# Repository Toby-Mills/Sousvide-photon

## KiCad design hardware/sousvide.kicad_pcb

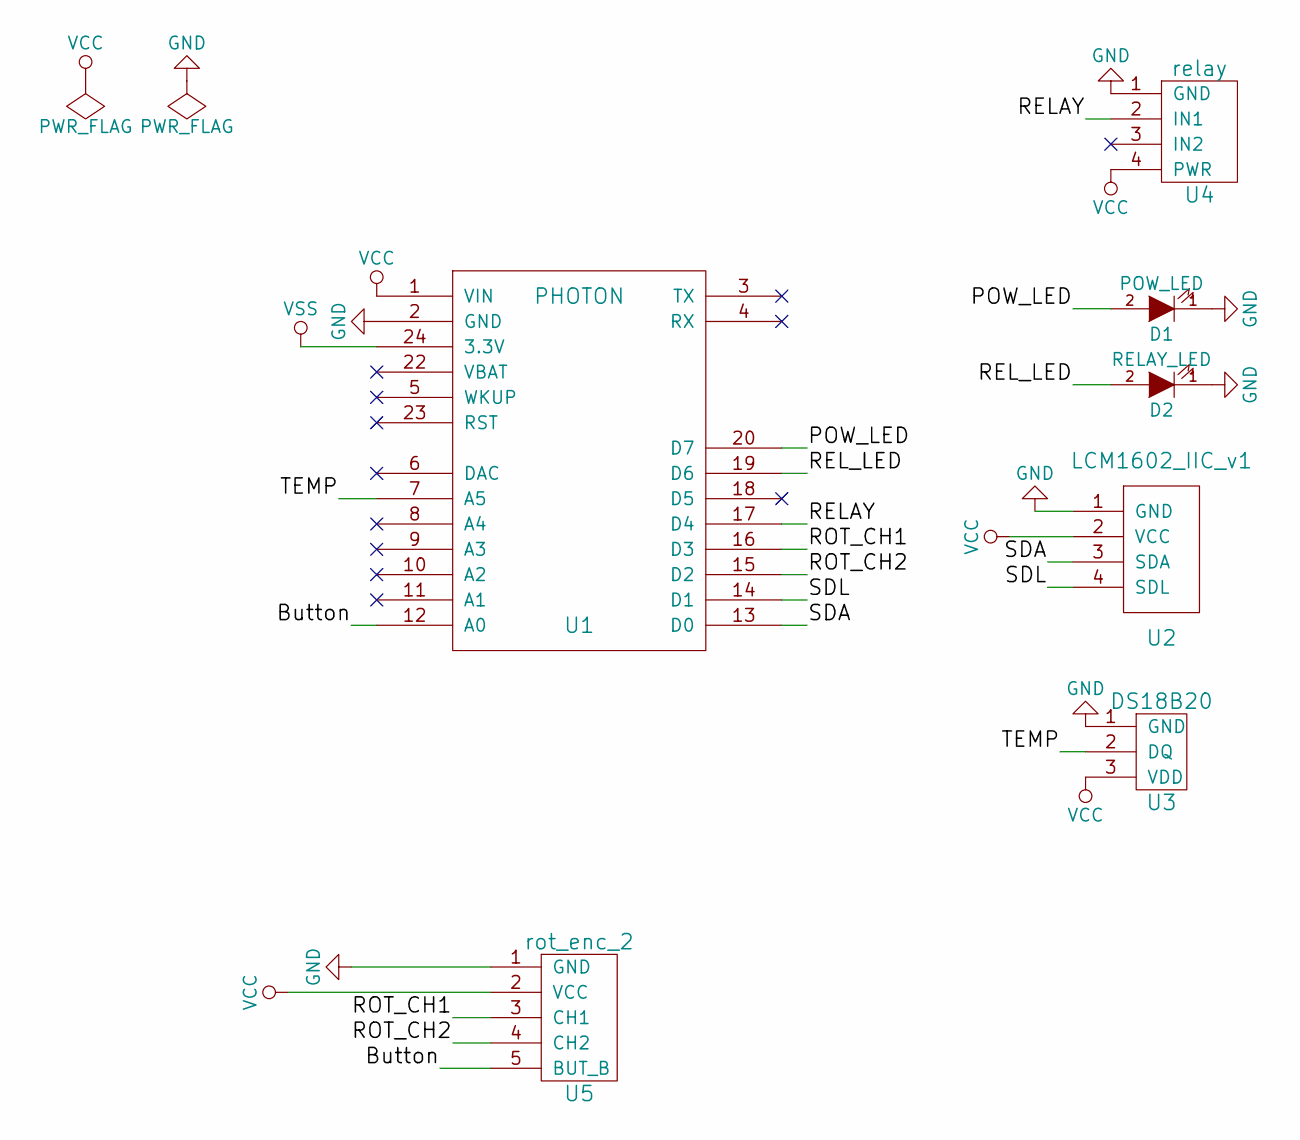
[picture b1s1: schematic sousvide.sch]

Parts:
D1: POW_LED; LED-5MM
D2: RELAY_LED; LED-5MM
U1: PHOTON; photon
U2: LCM1602_IIC_v1; Pin_Header_Straight_1x04
U3: DS18B20; Pin_Header_Straight_1x03
U4: relay; Pin_Header_Straight_1x04
U5: rot_enc_2; Pin_Header_Straight_1x05

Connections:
/Button: U1.12 (A0), U5.5 (BUT_B)
/POW_LED: D1.2 (A), U1.20 (D7)
/RELAY: U1.17 (D4), U4.2 (IN1)
/REL_LED: D2.2 (A), U1.19 (D6)
/ROT_CH1: U1.16 (D3), U5.3 (CH1)
/ROT_CH2: U1.15 (D2), U5.4 (CH2)
/SDA: U1.13 (D0), U2.3 (SDA)
/SDL: U1.14 (D1), U2.4 (SDL)
/TEMP: U1.7 (A5), U3.2 (DQ)
GND: D1.1 (K), D2.1 (K), U1.2 (GND), U2.1 (GND), U3.1 (GND), U4.1 (GND), U5.1 (GND)
VCC: U1.1 (VIN), U2.2 (VCC), U3.3 (VDD), U4.4 (PWR), U5.2 (VCC)
VSS: U1.24 (3.3V)

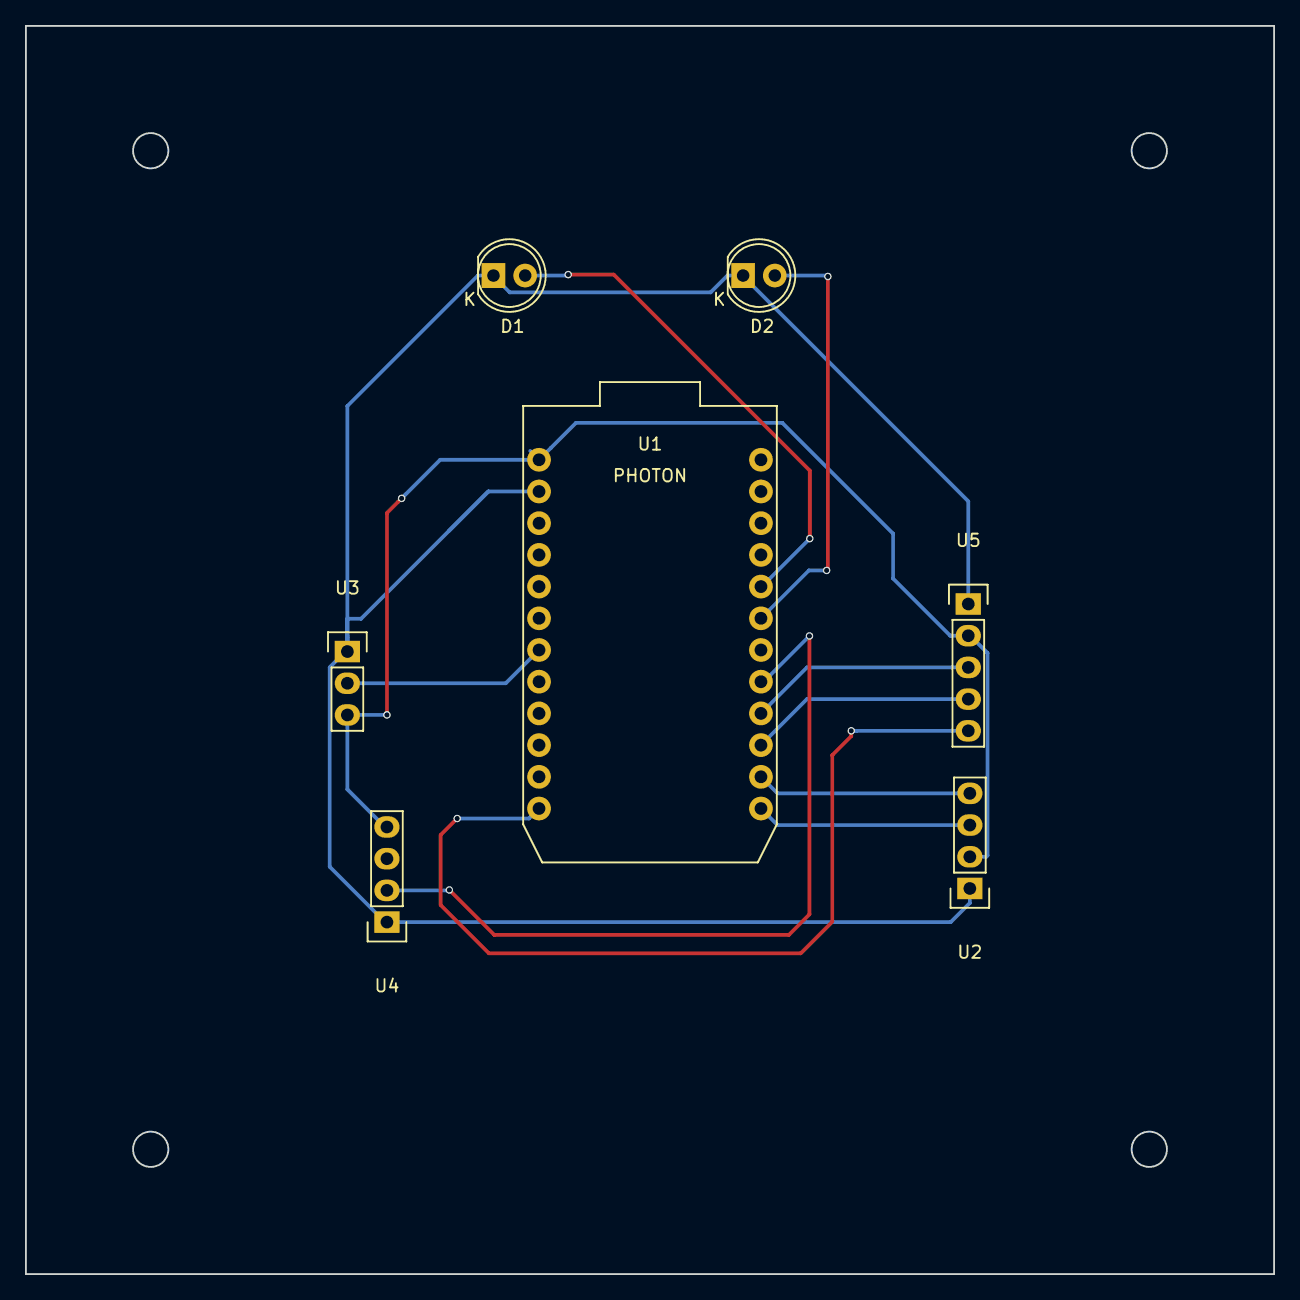
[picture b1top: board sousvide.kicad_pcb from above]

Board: 2 copper layers, 100.0 x 100.0 mm, 7 parts (0 on the bottom side), 11 nets.

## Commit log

2018-05-20 Commenting and formatting
2018-05-20 Removed unneeded makeChange code
2018-05-20 cleaned redraw screen code
    removed unneeded redrawscreeni variable
    renamed screenRedrawRelayRequest to lastScreenRedraw
2018-05-20 removed unneeded temp, ctemp and ctempm variables
2018-05-20 Removed old commented code
2018-05-20 removed unused atTemp, offset, uptime, atime variables
2018-05-20 refactored Setup() to call methods
2018-05-20 refactored code for setting desired temperature & updating display
2018-05-20 improved variable names
2018-05-20 removed unused getSavedTemp method
2018-05-20 removed unused setTitle method
2018-05-20 commenting and refactoring
2018-05-20 Removed unused variables
2018-05-20 bug fix
2018-07-18 Rotary Encoder adjusts target temp
2018-07-23 Power and Relay LED's added
2018-08-09 Exposed variables to Particle Cloud
2018-08-17 Added kicad files for controller board
2018-08-17 moved kicad designs to 'hardware' folder
2018-08-17 ignore bin files
2018-11-21 Improved screen draw, and added SetTemp mode
2018-11-22 Moved encoder reading to in setTemp mode only
2018-11-22 Reduced screen flicker
    Only redraw current temp, rather than whole screen with every new reading
2021-01-30 Updated firmware to 2.0.1
2021-01-30 Added blynk integration for Temp variables
2021-01-30 code cleanup
2021-01-31 Changed sensor reading interval to 1 second
2021-02-01 Added support for a Timer function
2021-02-01 refactored to not include token
2021-12-23 added mqtt
2021-12-23 removed blynk
